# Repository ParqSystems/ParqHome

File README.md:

ParqHome is a smart home automation system that controls household appliances in real time through a combination of custom hardware, IoT protocols, and cloud infrastructure. Users toggle devices on a React Native dashboard, which publishes MQTT commands to an ESP8266 microcontroller. The ESP8266 controls relays to switch appliances instantly, and any state change syncs back through the cloud to keep the UI synchronized. Physical switches continue to work independently for local control, ensuring the system remains functional even if cloud connectivity is lost.

The system is built on a custom PCB with an ESP8266 (ESP-12F), relay driver circuits, power regulation, and protection mechanisms. Communication happens through MQTT via HiveMQ Cloud, while the backend uses Express.js with MongoDB Atlas for state management and API services. Python automation services handle reliable message routing, and a React Native frontend provides real-time device control and status updates. Every component was designed and tested to solve real-world challenges in synchronizing distributed embedded systems with cloud infrastructure.

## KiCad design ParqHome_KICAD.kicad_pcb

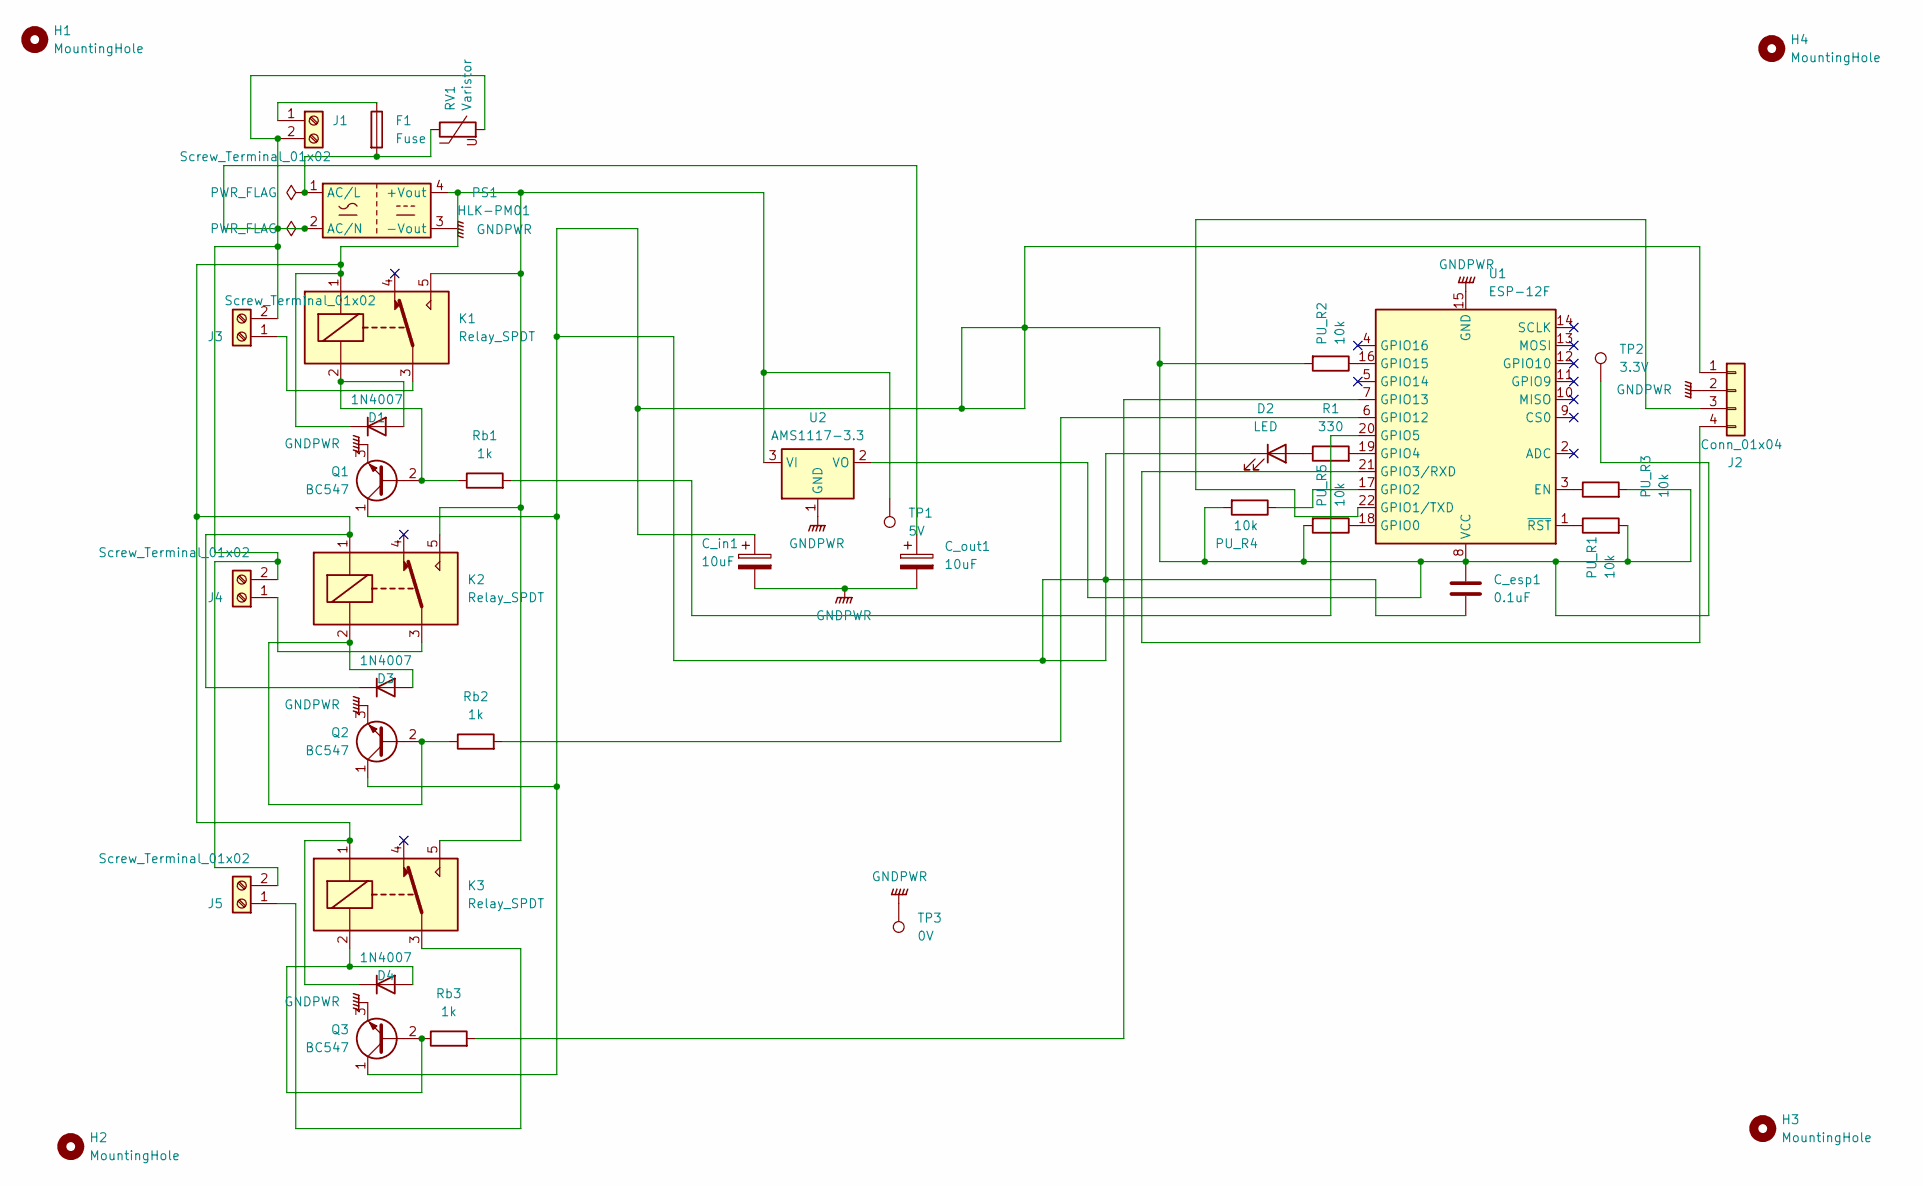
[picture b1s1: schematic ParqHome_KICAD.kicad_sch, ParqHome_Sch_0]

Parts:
C_esp1: 0.1uF; C_0805_2012Metric
C_in1: 10uF; CP_Radial_D6.3mm_P2.50mm
C_out1: 10uF; CP_Radial_D6.3mm_P2.50mm
D1, D3, D4: 1N4007; D_DO-41_SOD81_P10.16mm_Horizontal
D2: LED; LED_0805_2012Metric
F1: Fuse; Fuseholder_Clip-5x20mm_Littelfuse_520_Inline_P20.50x5.80mm_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
H1, H2, H3, H4: MountingHole; MountingHole_3.2mm_M3
J1, J3, J4, J5: Screw_Terminal_01x02; TerminalBlock_CUI_TB007-508-02_1x02_P5.08mm_Horizontal
J2: Conn_01x04; PinHeader_1x04_P2.54mm_Vertical
K1, K2, K3: Relay_SPDT; Relay_SPDT_SANYOU_SRD_Series_Form_C
PS1: HLK-PM01; Converter_ACDC_Hi-Link_HLK-PMxx
PU_R1, PU_R2, PU_R3, PU_R4, PU_R5: 10k; R_0805_2012Metric
Q1, Q2, Q3: BC547; TO-92_Inline
R1: 330; R_0805_2012Metric
RV1: Varistor; RV_Disc_D7mm_W3.4mm_P5mm
Rb1, Rb2, Rb3: 1k; R_0805_2012Metric
TP1: 5V; TestPoint_Bridge_Pitch2.54mm_Drill1.0mm
TP2: 3.3V; TestPoint_Bridge_Pitch2.54mm_Drill1.0mm
TP3: 0V; TestPoint_Bridge_Pitch2.54mm_Drill1.0mm
U1: ESP-12F; ESP-12E
U2: AMS1117-3.3; SOT-223-3_TabPin2

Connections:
GNDPWR: C_in1.2, C_out1.2, J2.2, PS1.3 (-Vout), Q1.3 (E), Q2.3 (E), Q3.3 (E), TP3.1, U1.15 (GND), U2.1 (GND)
unnamed: D1.2 (A), K1.2, Q1.2 (B), Rb1.1
unnamed: D1.1 (K), D3.1 (K), D4.1 (K), K1.1, K1.5, K2.1, K2.5, K3.1, K3.5, PS1.4 (+Vout), TP1.1, U2.3 (VI)
unnamed: D2.2 (A), R1.1
unnamed: C_esp1.1, C_esp1.2, C_in1.1, D2.1 (K), J2.1, PU_R1.2, PU_R2.2, PU_R3.2, PU_R4.2, PU_R5.2, Q1.1 (C), Q2.1 (C), Q3.1 (C), TP2.1, U1.8 (VCC), U2.2 (VO)
unnamed: D3.2 (A), K2.2, Q2.2 (B), Rb2.1
unnamed: D4.2 (A), K3.2, Q3.2 (B), Rb3.1
unnamed: F1.1, J1.1
unnamed: C_out1.1, J1.2, J3.2, J4.2, J5.2, PS1.2 (AC/N), RV1.2
unnamed: J2.3, U1.22 (GPIO1/TXD)
unnamed: J2.4, U1.21 (GPIO3/RXD)
unnamed: J3.1, K1.3
unnamed: J4.1, K2.3
unnamed: J5.1, K3.3
unnamed: F1.2, PS1.1 (AC/L), RV1.1
unnamed: PU_R3.1, U1.3 (EN)
unnamed: PU_R5.1, U1.18 (GPIO0)
unnamed: PU_R4.1, U1.17 (GPIO2)
unnamed: R1.2, U1.19 (GPIO4)
unnamed: Rb1.2, U1.20 (GPIO5)
unnamed: Rb2.2, U1.6 (GPIO12)
unnamed: Rb3.2, U1.7 (GPIO13)
unnamed: PU_R2.1, U1.16 (GPIO15)
unnamed: PU_R1.1, U1.1 (~RST)

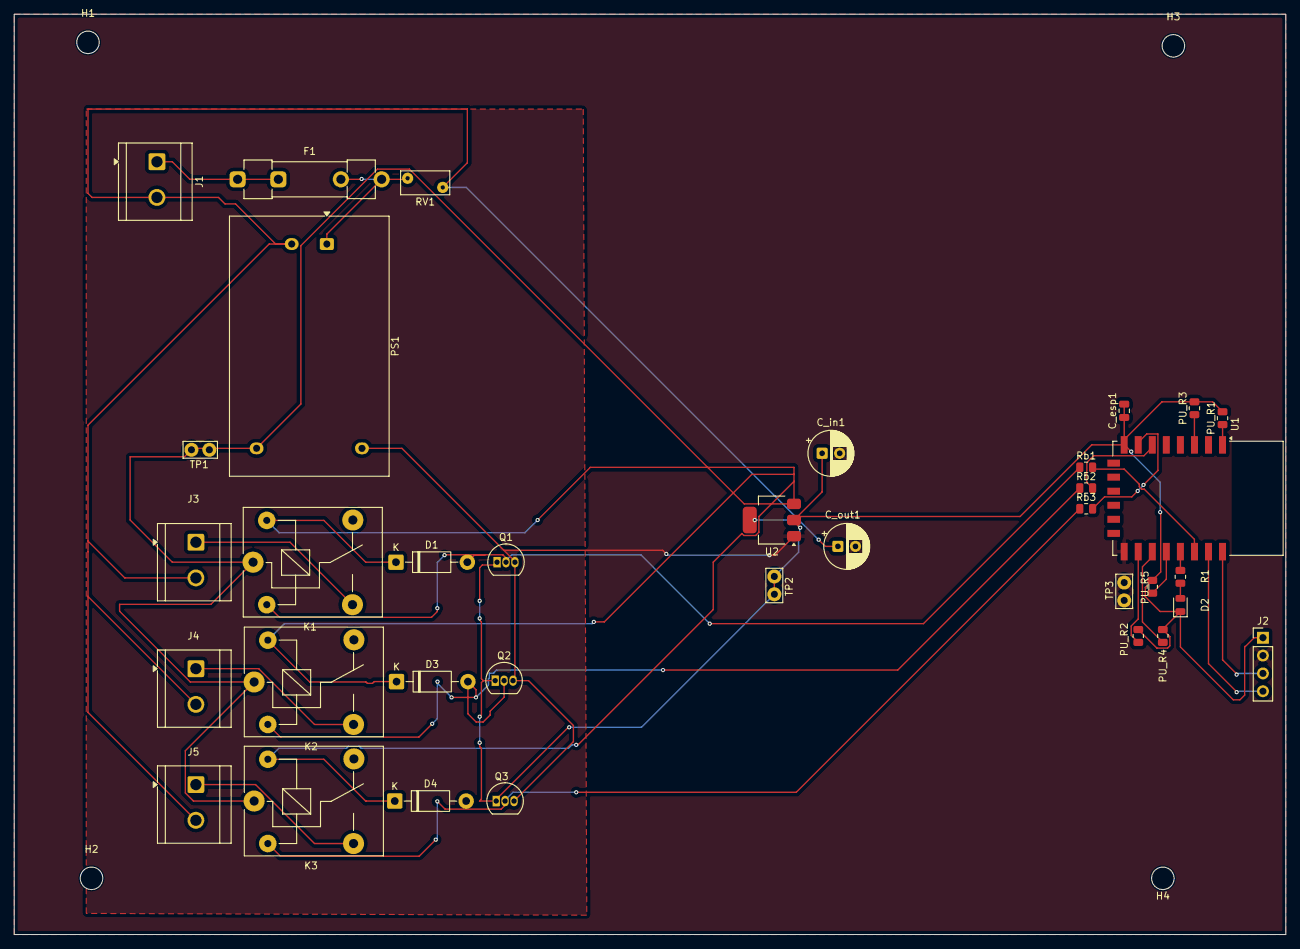
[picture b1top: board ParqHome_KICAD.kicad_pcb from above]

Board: 2 copper layers, 181.0 x 131.0 mm, 39 parts (0 on the bottom side), 24 nets.

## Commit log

2026-04-23 KiCad PCB Design upload
2026-04-25 Logo Decided
2026-06-13 Created the data automation process using MQTT
2026-06-13 MQTT messages sent across UI and ESP 8266
2026-06-13 Arduino code
2026-06-20 Added Home Automation project
2026-06-20 Fixed frontend tracked as submodule
